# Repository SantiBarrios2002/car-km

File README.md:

# car-km — household car kilometre tracker

Logs every ride of the family car automatically and works out who drove how many kilometres each month.

A small device in the car reads distance from the OBD-II port over Bluetooth and records each ride. Tapping an NFC fob says who is driving. Rides are uploaded over WiFi to a Raspberry Pi at home, and the family uses a phone web app to see monthly totals, assign untapped rides ("that was me") and export CSV.

```
 car                                              home
┌──────────────────────────────────────┐        ┌───────────────────────────────┐
│ Vgate iCar Pro ─BLE─► ESP32-S3 module │  WiFi  │ Raspberry Pi                  │
│ (OBD-II speed)        + carrier PCB   │ ─────► │ FastAPI + SQLite (app/)       │
│ PN532 NFC ─I²C─►      (supercap hold- │  HTTP  │ web app at /, device API      │
│ (who drives)           up, 5 V input) │        │ at /api/  ◄── family phones   │
└──────────────────────────────────────┘        └───────────────────────────────┘
```

## Status

| Part | Where | State |
| --- | --- | --- |
| Pi service + web app | `app/` | **In use** on the family Pi. |
| Carrier PCB | `hardware/carrier/` | Schematic done (ERC clean); first-pass board placed, autorouted and passing DRC. **Not reviewed, not ordered.** |
| Car device firmware | `firmware/` | Not started. Conventions are already fixed in `CLAUDE.md`. |

### Next step: pre-order checks for the carrier PCB

None of these have been done yet. They come before anything is sent to a fab; details and commands are in [`hardware/README.md`](hardware/README.md#next-step-pre-order-checks).

1. **Review the board in KiCad**: placement, power trace widths, the autorouted tracks.
2. **Check the 3D fit** against Waveshare's STEP model (stack height, standoffs, cable paths).
3. **Re-run ERC and DRC** after any changes.
4. **Export the Gerber and drill files** and inspect them in a Gerber viewer.

## Repository layout

```
app/                  Pi service: FastAPI + SQLite, web app and device API
  main.py             all routes (web app + device API), sections marked with # ----
  db.py               schema and SQLite helpers
  static/index.html   the whole web app: one file, vanilla JS, Spanish/English
install.sh            Pi install: venv, systemd unit, nightly backup cron (safe to re-run)
car-km.service        systemd unit template used by install.sh
hardware/             car device hardware: Waveshare module + custom carrier PCB
  README.md           hardware design document: start here for the electronics
  carrier/            KiCad 10 project (schematic + PCB)
  bom-rev2.csv        bill of materials
  vendor/             Waveshare schematic and mechanical drawing (PDF)
CLAUDE.md             working notes for Claude Code and contributors: conventions, hard rules, hardware facts
```

`data/` (database, device token, firmware images, backups) is created at runtime and is not committed.

## Pi service

### Install on the Pi

```bash
git clone <this repo> ~/car-km
cd ~/car-km && chmod +x install.sh && ./install.sh
```

The script creates a venv, installs a systemd unit (`car-km.service`, port 8080) and a nightly SQLite backup cron, then prints the Tailscale URL to share with the family. Logs: `journalctl -u car-km -f`.

### Using it

- Open `http://<pi-tailscale-name>:8080` on a phone (see *Links*). On iOS, Share → *Add to Home Screen* makes it feel like an app.
- The first visit asks *¿Quién eres?*; the answer is remembered on that phone.
- **Ajustes**: add the people. Optionally log the real odometer reading once; after that a ride can be logged by typing the new odometer reading instead of km.
- **Apuntar**: km (or odometer) → Guardar. Rides can be back-dated.
- **Resumen**: monthly totals per person, with unassigned rides highlighted and a *Fui yo* button; the CSV button exports the month.
- Language (es/en) and €/km are set in Ajustes.

### Links (family setup)

| Where | URL |
| --- | --- |
| Anywhere, phone with Tailscale | http://iot-hub.tail8fe499.ts.net:8080 |
| Same, by Tailscale IP (if the name doesn't resolve) | http://100.102.81.29:8080 |
| Home WiFi, no Tailscale needed | http://192.168.1.140:8080 |
| API docs | http://iot-hub.tail8fe499.ts.net:8080/api/docs |

### Giving family members access (Tailscale)

At home the LAN link works for anyone on the WiFi. From outside, each person needs Tailscale. Prefer **sharing the Pi** over inviting people into the tailnet: someone you share with can reach only `iot-hub`, not your other devices.

1. In https://login.tailscale.com/admin/machines, open the **⋯** menu on `iot-hub` → **Share…** and copy the invite link.
2. Send it to the person. They install Tailscale (iOS/Android), sign in with their own Google/Apple/Microsoft account and open the link. They get their own free tailnet with `iot-hub` in it.
3. On their phone: Tailscale on → open the link above → Share / ⋮ → *Add to Home Screen*.
4. To revoke: admin console → **Machines** → `iot-hub` → **Share…** (or the **Sharing** tab) and remove them.

Alternatively, **Users → Invite users** makes them full tailnet members. That's simpler when they have many devices, but by default they can then reach every machine, so restrict them in **Access controls**.

### Device API (used by the car device)

| Method | Path | Auth | Purpose |
| --- | --- | --- | --- |
| POST | `/api/rides/batch` | bearer | JSON array of rides; idempotent on `(device_id, start_ts)` |
| GET | `/api/fobs` | none (also used by the web app) | fob → user map; send `If-None-Match` with the last ETag to get a 304 |
| GET | `/api/time` | bearer | server unix time, for setting the RTC |
| GET | `/api/firmware` | bearer | latest `firmware.bin`; send `X-Version` to get a 304 when current |

Bearer = `Authorization: Bearer <token>`. The token is in `data/device_token`, created on first start and shown in Ajustes. OTA images go in `data/firmware/` (`firmware.bin` + `version.txt`).

Ride object:

```json
{"device_id":"meriva-1","start_ts":1759742400,"end_ts":1759744230,"km":23.4,
 "fob_uid":"04A1B2C3D4E580","source":"obd","fw":"0.3.1","end_reason":"brownout"}
```

Interactive docs at `/api/docs`.

### Development

```bash
python3 -m venv .venv && .venv/bin/pip install -r requirements.txt
.venv/bin/uvicorn app.main:app --reload --port 8081
```

Port 8081 lets the dev server run alongside the live service on 8080. Run from the repo root: the default paths under `data/` are relative to the working directory.

### Security model

There are no logins: the app is reachable only on the home LAN and over Tailscale, and a household km log doesn't need more. The device API uses a bearer token. Don't expose port 8080 to the internet; if wider access is ever needed, put it behind Tailscale Serve or a reverse proxy with authentication.

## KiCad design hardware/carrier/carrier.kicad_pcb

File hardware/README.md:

# car-km hardware — Rev 2: Waveshare ESP32-S3-Touch-LCD-2.8 + carrier PCB

The car device is an off-the-shelf **Waveshare ESP32-S3-Touch-LCD-2.8** (ESP32-S3, 2.8" touch display, RTC, Li-ion charger) mounted on a small custom **carrier PCB**. The carrier takes 5 V from the car's USB port, holds the module up for a few seconds after the ignition cuts power (so the ride can be saved), tells the firmware when that happens, and breaks out the PN532 NFC reader and a debug UART. Distance comes from a **Vgate iCar Pro** BLE OBD-II dongle, which needs no wiring.

## Status

| Item | State |
| --- | --- |
| Module facts | Verified against Waveshare's schematic and 2D drawing (`vendor/`), 2026-10-06. |
| Carrier schematic | `carrier/carrier.kicad_sch`, KiCad 10, ERC clean (0 violations). |
| Carrier PCB | `carrier/carrier.kicad_pcb`, first pass: placed, autorouted, DRC clean. **Not reviewed by a person, not ordered.** |
| Parts | Nothing bought yet except the OBD dongle (`bom-rev2.csv`). |

## Next step: pre-order checks

None of these have been done yet. Work through them in order before sending anything to a fab. All commands run from the repo root.

**1. Review the board in KiCad.** Open `hardware/carrier/carrier.kicad_pro`, then the PCB editor. Look at:
- **Routing:** the signals were autorouted (Freerouting) and nobody has looked at them yet. Tidy anything odd, especially the long USB_5V run to the fallback R3/D2. Those two parts aren't fitted by default, so that track could be shortened or moved.
- **Power trace widths:** 0.6 mm, which is the most J3's 1.0 mm-pitch pads and J1's VBUS pins allow. Widen the open runs (J1 → F1 → D1/JP1 → J3, J5 → JP2 → caps) where there is room.
- **Connector positions** against the real stack (see step 2): J1 on the bottom edge, J3 on the left edge, J5 on the right edge, J2 on the top edge.
- **Silkscreen:** pin-1 marks, cap polarity, the JP1/JP2 notes.
- After any edit, refill zones (`B`) before checking.

**2. Check the 3D fit.**
- Install the 3D models (`sudo apt install kicad-packages3d`, or use a KiCad install that has them).
- Download `ESP32-S3-Touch-LCD-2.8_3D.zip` from the [Waveshare wiki](https://www.waveshare.com/wiki/ESP32-S3-Touch-LCD-2.8) into `vendor/`. Don't commit it; it's 20 MB.
- Export the carrier: `kicad-cli pcb export step --subst-models -o hardware/carrier/carrier.step hardware/carrier/carrier.kicad_pcb`.
- Combine the two in FreeCAD (or the KiCad 3D viewer): the module sits on top, parts side facing the carrier, on 8 mm standoffs. Check:
  - **The gap between the boards.** The module's back parts are 6 mm tall, so about 2 mm is left. The carrier's inner face has no parts, but the through-hole leads of J2, J4, C1 and C4 stick out of it: trim them flush or check they clear.
  - **Total depth:** module 10 mm + standoffs 8 mm + carrier 1.6 mm + supercaps 20 mm standing (or ~9 mm lying flat).
  - **Cable paths:**
    - SH-12 cable from J3 round the left edge to module J8, which is in the lower-left quadrant of the module's back, about 12 mm from its left edge;
    - 2-pin cable from J5 to module J1 (BAT);
    - PN532 cable from J2.
  - **USB-C clearance:** a plug in the carrier's J1 near the module's own USB-C, which sits bottom centre.

**3. Re-run ERC and DRC** after any change:

```bash
kicad-cli sch erc --severity-all -o /tmp/erc.rpt hardware/carrier/carrier.kicad_sch
kicad-cli pcb drc --schematic-parity --severity-all -o /tmp/drc.rpt hardware/carrier/carrier.kicad_pcb
```

Expected: ERC 0 violations; DRC 0 errors, 0 unconnected, 0 parity issues. Two warnings are accepted: J1's library silkscreen runs off the board edge where the receptacle overhangs it.

**4. Export the fab files and inspect them.**

```bash
mkdir -p hardware/carrier/fab
kicad-cli pcb export gerbers --check-zones -l F.Cu,B.Cu,F.Paste,B.Paste,F.SilkS,B.SilkS,F.Mask,B.Mask,Edge.Cuts \
  -o hardware/carrier/fab/ hardware/carrier/carrier.kicad_pcb
kicad-cli pcb export drill --excellon-separate-th --generate-map -o hardware/carrier/fab/ hardware/carrier/carrier.kicad_pcb
```

Open the result in `gerbview` (ships with KiCad) or the fab's online viewer before uploading. The board is 2 layers, 1.6 mm, 69.0 × 49.9 mm, with a 0.2 mm minimum clearance and 0.15 mm minimum track (standard JLCPCB/PCBWay rules). `fab/` is not committed.

**After the boards arrive** (before the first car test):
- Change the module's R7 to ≥ 200 kΩ (see *Charge current*).
- Do the bench checks under *Still to verify*.

## The Waveshare module (from its schematic)

| Item | Fact | Consequence |
| --- | --- | --- |
| J8 "12-pin header" | **JST SH 1.0 mm, 12 pins** (`SH1.0-12P`) | The carrier connects with a 12-way SH cable; its J3 is an SH-12 socket. |
| J8 pinout | 1 GND · 2 **USB_5V** · 3 D− (IO19) · 4 D+ (IO20) · 5 GND · 6 3V3 · 7 SCL (IO10) · 8 SDA (IO11) · 9 UART_TXD (IO43) · 10 UART_RXD (IO44) · 11 **GPIO18** · 12 **GPIO15** | 5 V in, I²C, two spare GPIOs and UART on one cable. |
| USB → system | USB_5V → **D3 B5819WS** Schottky → VCC → **ME6217C33** LDO → 3V3 | USB has priority; VCC ≈ USB_5V − 0.3 V. D3 stops the battery rail back-feeding USB_5V. |
| Battery → system | BAT → **Q1 AO3401** (gate: R2 100 k to BAT, pulled low by **T2** when `BAT_Control` = IO7 is high, or by Key1) → **Q2 AO3401** (gate = USB_5V, R29 100 k to GND) → VCC | The battery path is on only when USB is absent **and** the firmware has driven IO7 high. Q2's body diode also conducts once VCC drops ~0.6 V below BAT. |
| Charger | **ETA6098** switching Li-ion charger, input = USB_5V, **RISET R7 = 82 kΩ → 2 A**, CV 4.2 V, 130 mA termination, restarts at −160 mV, input 4.5–5.5 V | Charges whatever is on the battery connector to 4.2 V. |
| Battery connector | J1, labelled **"PH1.25 2P"**: the 1.25 mm MX1.25 / Molex PicoBlade-compatible part (not JST PH 2.0 or GH). Pin 1 = BAT. | The supercap bank plugs in here, via the carrier's J5. |
| Pull-ups | R30 10 k to 3V3 on IO15 (SD_D2), R35 10 k on IO18 (SD_D1) | IO15 already has a pull-up, so the power-loss sense must drive it actively low. |
| BAT_ADC | IO8 reads BAT through 200 k / 100 k | Vbat = 3 × Vadc. |
| Backlight | NPN T3 on **IO5** | Turned off first when power is lost. |
| Antenna | Ceramic chip antenna (CA-C03) + U.FL, **top-left corner** in back view (ESP32 module upper-left, USB-C bottom centre) | Copper keep-out on the carrier under that corner. |
| Mechanical | PCB 69.00 × 49.90 mm, glass 73.06 × 50.54 mm, 10.0 mm total, **6.0 mm of parts on the back**. 4 holes on a **60.00 × 41.00 mm** grid, 4.50 mm in from the edges, Ø ≈ 2.7 mm (M2.5) | The carrier copies the outline and holes; standoffs ≥ 8 mm. |

## Carrier design

Schematic: `carrier/carrier.kicad_sch` (the source of truth for every net).

```
car USB ─ J1 USB-C ─ F1 PTC 1.1 A ─┬─ TVS1 SMAJ5.0A ─ GND
            VIN_CAR      VIN_FUSED ├─ R8 4k7 bleeder ─ GND
                                   ├─ R1 100k ─┬─ R2 11k3 ─ GND
                                   │           └─ U2 TPS3808G01 SENSE      ~RESET → J3.12 (IO15) = PWR_SENSE
                                   │              (VDD = module 3V3 via J3.6, C3 100n)
                                   └─ D1 SS34 ∥ JP1 (bridged) ─┬─ C2 10µF   USB_5V → J3.2
                                                               └─ TP1

module J1 (BAT) ─ cable ─ J5 PicoBlade ─ JP2 (bridged) ─ C1 5F/2.7V ─┬─ C4 5F/2.7V ─ GND
                                                          R4 10k ∥ C1  R5 10k ∥ C4
```

The carrier only protects (F1, TVS1), senses (U2), balances (R4/R5) and connects. Charging and switching to the caps happen on the module.

- **Hold-up.** The module's ETA6098 charges the 2 × 5 F bank (2.5 F, 5.4 V rated) to 4.2 V. When the car cuts power, USB_5V collapses (R8 bleeds it down; the module's D3 stops the board holding it up), Q2 turns on and the board runs from the caps. **Hold-up ≈ 5–7 s** with the backlight off: 2.5 F × (4.2 − 3.6 V) ÷ 0.2 A ≈ 7 s from a full bank, less because the charger only tops up after a 160 mV drop (~4.04 V). Saving the ride takes well under a second.
- **Power-loss sense (U2).** A TPS3808G01 supervisor watches VIN_FUSED through R1/R2 and drives IO15 low with its open-drain `~RESET`; the module's R30 is the pull-up.
  - Trip point: 0.405 V × (1 + 100 k / 11.3 k) = **3.99 V falling**. `~RESET` releases 20 ms after VIN_FUSED recovers (CT open).
  - U2 runs from the module's 3V3, which the caps hold up, so IO15 stays low for the whole hold-up. A supervisor powered from the car side would let IO15 float back high once the car rail fell below ~1 V.
  - A plain resistor divider can't do this job: R30 keeps IO15 high whether the car is on or off.
- **JP1 is bridged by default** (D1 bypassed). D1's drop plus the PTC and cable would leave ~4.4 V at J8, below the ETA6098's 4.5 V minimum input. D1 only matters in the fallback configuration.
- **Charge current.** Everything the module draws, up to 2 A of charge current included, comes in through J8 pin 2: one SH contact rated about 1 A, behind F1 (1.1 A hold). **Change the module's R7 (0402, back side) from 82 k to ≥ 200 k (≈ 0.8 A)** before the first car test. Recharging an empty bank then takes ~15 s instead of ~5 s.
- **Firmware duties:** drive IO7 (`BAT_Control`) high at boot and never low, otherwise the caps are never connected. Leave the microSD slot empty or use 1-bit SD mode, because IO15 is also SD_D2.

### Fallback configuration

This is for the case where the bench test shows the module's charger misbehaving with a capacitor load. Footprints for the Rev 1 circuit are on the board, unpopulated (DNP):
- **R3** (22 Ω, 1 W) from USB_5V to VCAP;
- **D2** (SS34) from VCAP back to USB_5V.

To switch over:
1. Cut JP1, so that D1 blocks back-feed into the car port.
2. Cut JP2.
3. Leave J5 unconnected.
4. Fit R3 and D2.

The caps then charge to ~4.7 V from the 5 V side and discharge into USB_5V through D2. Hold-up ≈ 2.5 F × (4.4 − 3.9 V) ÷ 0.2 A ≈ 6 s.

### Nets (summary)

| Net | Pins |
| --- | --- |
| VIN_CAR | J1 VBUS (A4, A9, B4, B9), F1.1 |
| VIN_FUSED | F1.2, TVS1 K, D1 A, JP1.1, R1.1, R8.1 |
| USB_5V | D1 K, JP1.2, C2.1, J3.2, TP1, R3.1 (DNP), D2 K (DNP) |
| SENSE_DIV | R1.2, R2.1, U2.5 SENSE |
| PWR_SENSE | U2.1 ~RESET, J3.12 |
| BAT | J5.1, JP2.1 |
| VCAP | JP2.2, C1 +, R4.1, TP2, R3.2 (DNP), D2 A (DNP) |
| VCAP_MID | C1 −, C4 +, R4.2, R5.1 |
| +3V3 | J3.6, J2.1, U2.6 VDD, U2.3 ~MR, C3.1 |
| SCL / SDA | J3.7 / J3.8 → J2.4 / J2.3 |
| NFC_IRQ | J3.11, J2.5 |
| UART_TX / UART_RX | J3.9 / J3.10 → J4.1 / J4.2 (module TXD / RXD) |
| USB_CC1 / USB_CC2 | J1 A5 / B5 → R6 / R7 5.1 k → GND |
| GND | J1 GND + shell, TVS1 A, R2, R5, R6, R7, R8, C2, C3, C4 −, U2.2, J2.2, J3.1, J3.5, J3/J5 mounting tabs, J4.3, J5.2, H2–H4 |

Not connected: J3.3 / J3.4 (USB D±), U2.4 CT (open = 20 ms delay), J1 D± and SBU. H1 is a bare hole.

### Connectors and cables

| Ref | Part | Mates with | Cable |
| --- | --- | --- | --- |
| J1 | USB-C 16-pin receptacle (HRO TYPE-C-31-M-12), power only | car USB cable | — |
| J3 | JST **SM12B-SRSS-TB** (SH 1.0 mm, 12-pin, side entry) | module J8 | 12-way SH, 80–120 mm, **same-side (type A)** so pin 1 maps to pin 1. Check with a meter before first power-up. |
| J5 | Molex **53261-0271** (PicoBlade 1.25 mm, 2-pin, SMD right angle) | module J1 (BAT) | 2-way 1.25 mm (Molex 51021-0200 housing both ends), 80 mm. Mind polarity: pin 1 = BAT on both. |
| J2 | JST **S5B-PH-K-S** (PH 2.0 mm, 5-pin, right angle) | PN532 module (DIP switch set to I²C) | 5-way PH to Dupont, 150–250 mm. Pins: 3V3, GND, SDA, SCL, IRQ. |
| J4 | 1 × 3 2.54 mm header | USB-UART dongle | J4.1 = module TX → dongle RX, J4.2 = module RX ← dongle TX, J4.3 = GND. |

## PCB layout (`carrier/carrier.kicad_pcb`)

- **Outline and stack:**
  - 69.00 × 49.90 mm, R2 corners, 2 layers, 1.6 mm.
  - The module sits on top, parts side down, on **8 mm M2.5 standoffs**; the carrier is behind it.
  - KiCad's top view is the carrier's outer face, which matches the module's back view: antenna top-left, USB-C bottom.
- **All parts are on the outer face** (F.Cu). The inner face stays empty because only ~2 mm is left under the module's 6 mm-tall back parts.
- **Holes:** Ø2.7 at (4.5, 4.5), (64.5, 4.5), (4.5, 45.5), (64.5, 45.5) in module coordinates (origin at the bottom-left, back view).
  - H1, top-left, sits inside the antenna keep-out and is a bare NPTH with no copper.
  - H2–H4 are plated and tied to GND.
- **Antenna keep-out:** 25 × 12 mm in the top-left corner, no copper on either layer, outlined on the silkscreen.
- **Placement:**
  - edges: J1 on the bottom edge, J3 on the left edge (opening outward, cable wraps round to J8), J5 on the right edge, J2 on the top edge right of the keep-out;
  - J4 bottom right;
  - supercaps C1/C4 top right;
  - car-input parts (F1, TVS1, D1/JP1) between J1 and J3;
  - sense circuit (U2, R1/R2, C3) next to J3.
- **Net classes** (stored in `carrier.kicad_pro`):

  | Class | Track | Via | Nets |
  | --- | --- | --- | --- |
  | Power | 0.6 mm | 0.8 / 0.4 mm | VIN_CAR, VIN_FUSED, USB_5V, BAT, VCAP, VCAP_MID |
  | GND | 0.4 mm | 0.6 / 0.3 mm | GND |
  | Default | 0.25 mm | 0.6 / 0.3 mm | all signals |

  Clearance is 0.2 mm everywhere. The 0.15 mm minimum track width allows the necked-down +3V3 entry into U2's SOT-23 pads.
- **GND:**
  - pours on both layers;
  - a fan-out via next to every SMD GND pad;
  - stitching vias across the board.
  F.Cu has track keep-outs under the J1, J3 and J5 bodies.
- **Routing:** Freerouting 2.5 via Specctra DSN/SES, with GND left to the pours. This is a first pass to tidy by hand (step 1 of the pre-order checks).

## Firmware hooks (ESP-IDF, Waveshare BSP)

| Signal | GPIO | Use |
| --- | --- | --- |
| BAT_Control | IO7 | **Output high at boot**, first line of `app_main`. Keeps Q1 on so the caps carry the board when power is lost. |
| BAT_ADC | IO8 | Vbat = 3 × Vadc. Show "backup OK" above 3.9 V; warn if the caps never reach 4.0 V. |
| PWR_SENSE | IO15 | Input; falling edge = car power lost → brownout handler. |
| LCD_BL | IO5 | Backlight; switched off first in the brownout handler. |
| NFC_IRQ | IO18 | Input; falling edge = PN532 has a tag. |
| I²C | IO10 SCL / IO11 SDA | Shared: PN532 0x24, PCF85063 RTC 0x51, QMI8658 IMU 0x6B. |
| Key_BAT | IO6 | Module button; unused. |

Brownout handler: backlight off → stop BLE polling → write `ride/live` → mark the ride closed → halt (`while (1) vTaskDelay`). In the halt loop, if IO15 reads high again (ignition back on while the caps still hold the board, so no power-on reset happens), call `esp_restart()`; U2's 20 ms release delay debounces this. On the next boot a leftover `ride/live` is closed and queued.

## Still to verify

Verified from Waveshare's files: J8 pitch and pinout, USB_5V on J8, power path, charger current, outline and hole grid, antenna position, IO15/IO18 pull-ups.

- [ ] Hole diameter: the STEP only shows a 4.3 mm ring. Measure it, or use Ø2.7 / M2.5 either way.
- [ ] Bench, supercaps:
  1. Caps on module J1, USB in; BAT should reach ~4.2 V (BAT_ADC or a meter).
  2. Set IO7 high, pull USB and time the hold-up with the backlight off. Target ≥ 5 s.
  3. Repeat on a 1 A-limited supply to imitate a weak car port.
- [ ] Bench: module current with backlight on/off and WiFi on/off (USB meter).
- [ ] SH cable is same-side (type A): check with a meter before first power-up.
- [ ] The car's USB port really goes dead at key-out.

## Bill of materials

`bom-rev2.csv`. Revision notes:
- **First Rev 2 draft:**
  - J3 is an SH-12 socket (not 2.54 mm);
  - J5 1.25 mm added;
  - D1 kept but bypassable;
  - R3/D2 kept as fallback footprints;
  - SH and 1.25 mm cables added.
- **2026-10-06 review (schematic rev A):**
  - U2 TPS3808G01 + C3 power-loss sense (R2 47 k → 11.3 k);
  - R8 4.7 k bleeder;
  - JP1 bridged by default;
  - J5 = Molex 53261-0271;
  - supercaps renamed C1a/C1b → C1/C4;
  - H1 changed to a bare NPTH;
  - holes, jumpers and test points dropped from the BOM.

## Later: Rev 2b

PN532 chip with a printed antenna on the carrier (NXP AN1445). This needs a NanoVNA for antenna tuning, and only makes sense once Rev 2 works.

## Sources

- Waveshare [ESP32-S3-Touch-LCD-2.8 wiki](https://www.waveshare.com/wiki/ESP32-S3-Touch-LCD-2.8): schematic and 2D drawing, copied into `vendor/` as `ESP32-S3-Touch-LCD-2.8_schematic.pdf` and `ESP32-S3-Touch-LCD-2.8_2D.pdf`; STEP model (not committed).
- ETA6096 datasheet via [LCSC](https://wmsc.lcsc.com/wmsc/upload/file/pdf/v2/lcsc/2307171444_etasolution-ETA6096D3K_C7465538.pdf). It is the same family as the module's ETA6098: RISET 82 k → 2 A, CV 4.2 V, 130 mA termination, 4.5–5.5 V input.
- TI TPS3808 datasheet: adjustable version (G01) with a 0.405 V threshold, open-drain `~RESET`, CT open = 20 ms delay.

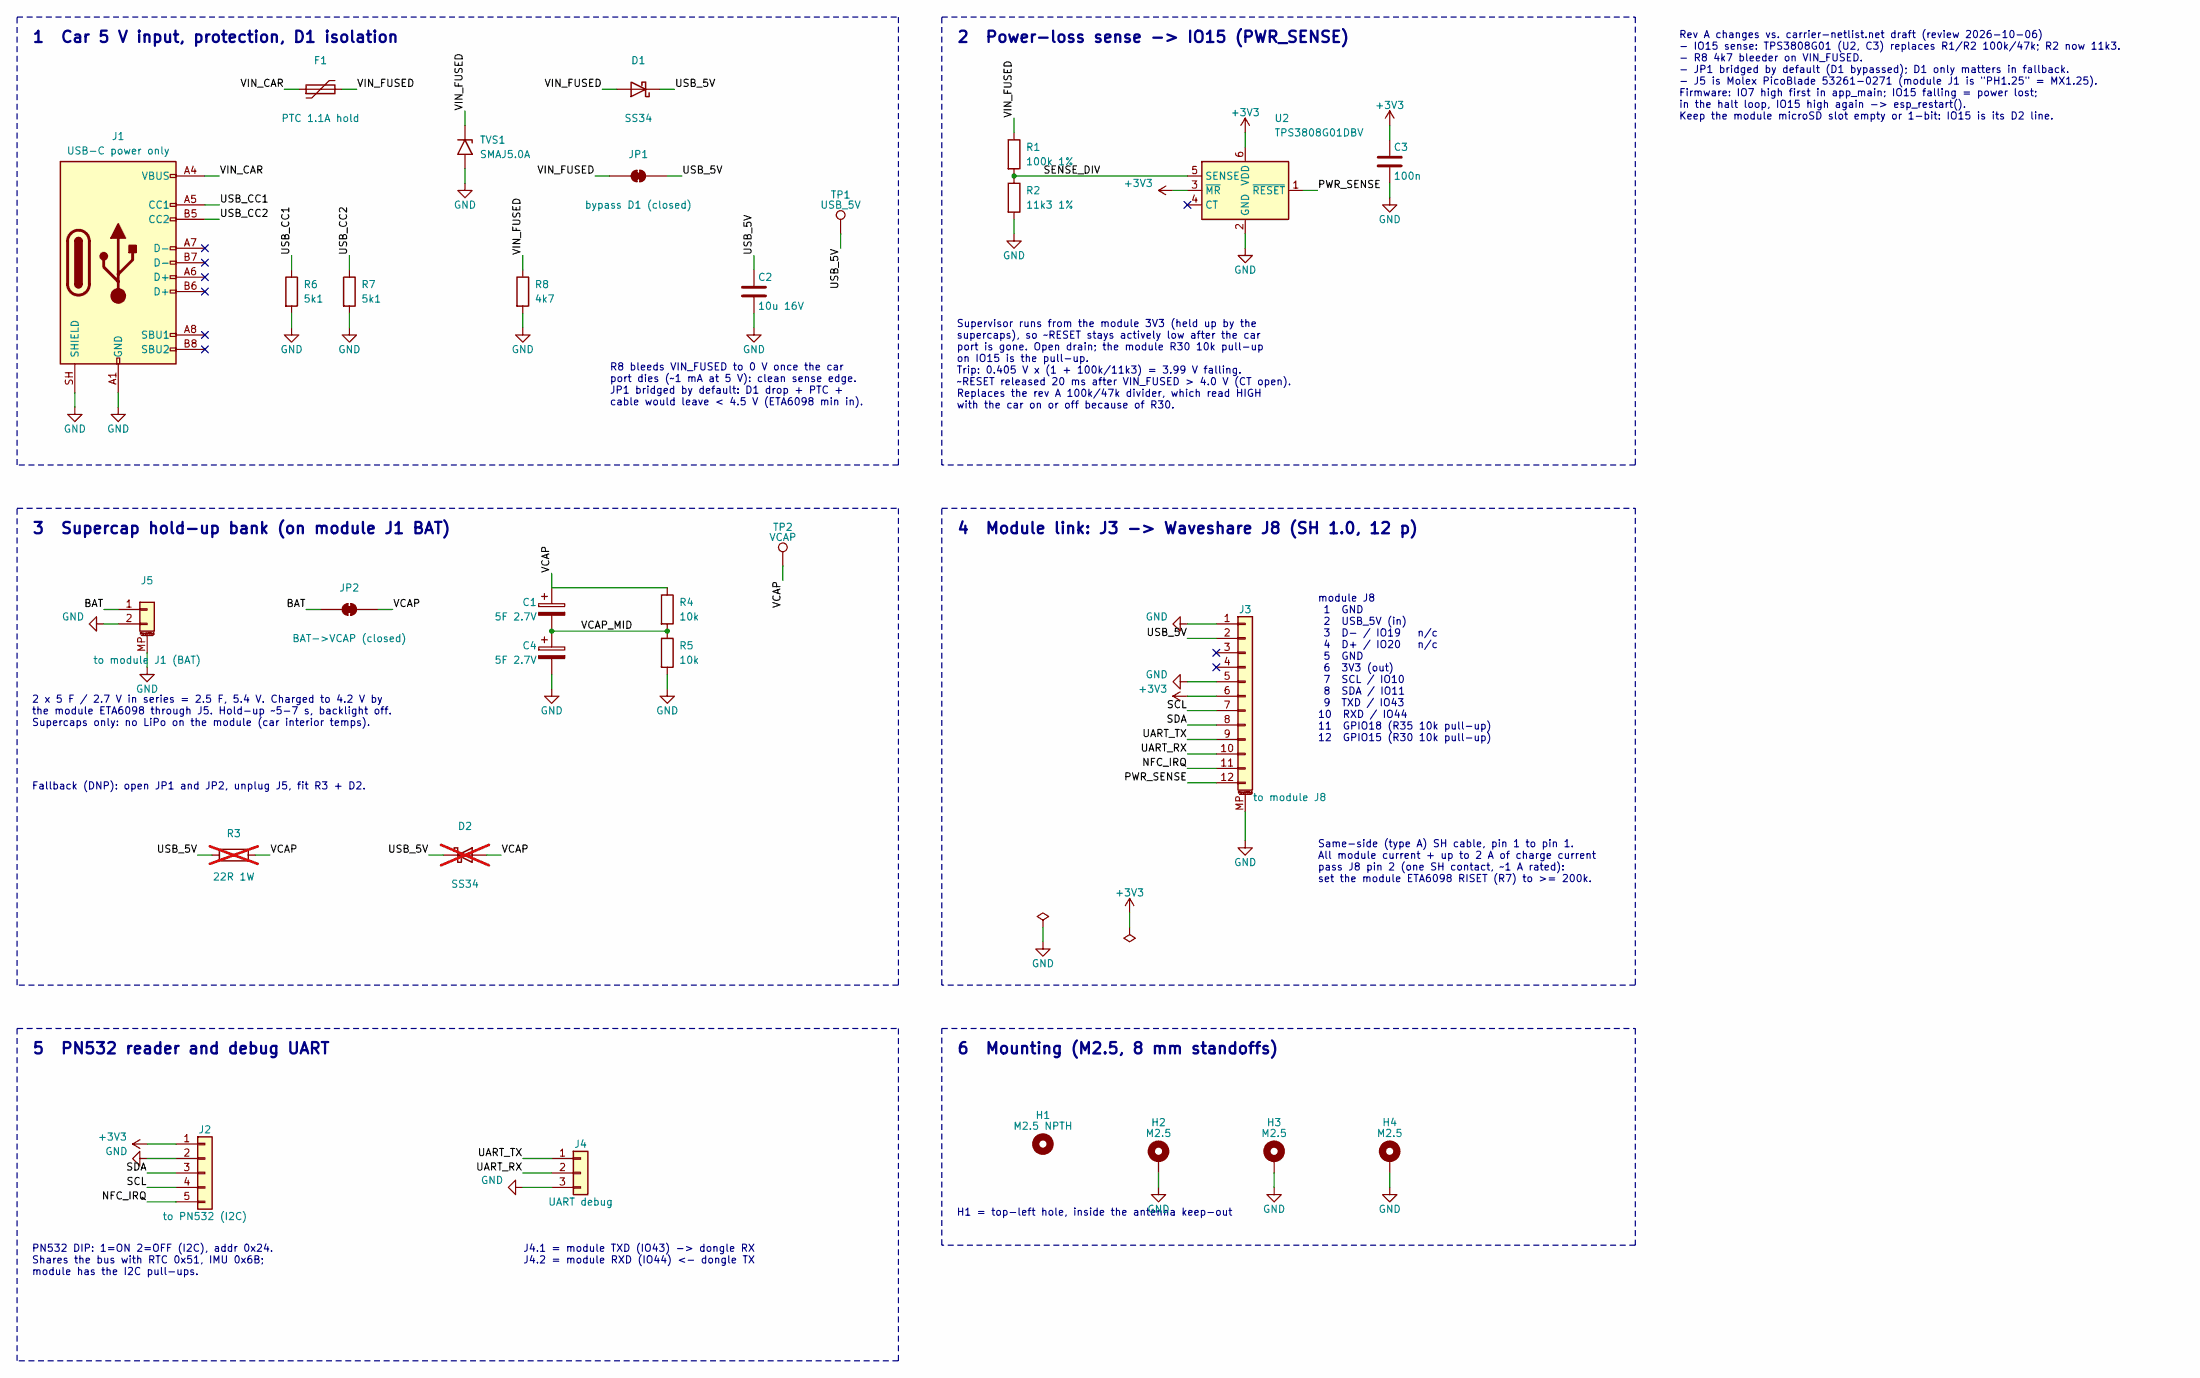
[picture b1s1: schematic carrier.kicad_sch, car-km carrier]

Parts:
C1, C4: 5F 2.7V; CP_Radial_D8.0mm_P3.50mm; MPN Eaton HB0820-2R5505-R class, ESR <= 0.5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
C2: 10u 16V; C_0805_2012Metric
C3: 100n; C_0805_2012Metric
D1: SS34; D_SMA
D2: SS34; D_SMA; not fitted
F1: PTC 1.1A hold; Fuse_1812_4532Metric
H1: M2.5 NPTH; MountingHole_2.7mm_M2.5
H2, H3, H4: M2.5; MountingHole_2.7mm_M2.5_Pad
J1: USB-C power only; USB_C_Receptacle_HRO_TYPE-C-31-M-12; MPN HRO TYPE-C-31-M-12
J2: to PN532 (I2C); JST_PH_S5B-PH-K_1x05_P2.00mm_Horizontal; MPN JST S5B-PH-K-S
J3: to module J8; JST_SH_SM12B-SRSS-TB_1x12-1MP_P1.00mm_Horizontal; MPN JST SM12B-SRSS-TB
J4: UART debug; PinHeader_1x03_P2.54mm_Vertical
J5: to module J1 (BAT); Molex_PicoBlade_53261-0271_1x02-1MP_P1.25mm_Horizontal; MPN Molex 53261-0271
JP1: bypass D1 (closed); SolderJumper-2_P1.3mm_Bridged_RoundedPad1.0x1.5mm
JP2: BAT->VCAP (closed); SolderJumper-2_P1.3mm_Bridged_RoundedPad1.0x1.5mm
R1: 100k 1%; R_0805_2012Metric
R2: 11k3 1%; R_0805_2012Metric
R3: 22R 1W; R_2512_6332Metric; not fitted
R4, R5: 10k; R_0805_2012Metric
R6, R7: 5k1; R_0805_2012Metric
R8: 4k7; R_0805_2012Metric
TP1: USB_5V; TestPoint_Pad_D1.5mm
TP2: VCAP; TestPoint_Pad_D1.5mm
TVS1: SMAJ5.0A; D_SMA
U2: TPS3808G01DBV; SOT-23-6; MPN TPS3808G01DBVR

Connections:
+3V3: C3.1, J2.1, J3.6, U2.3 (~MR), U2.6 (VDD)
/BAT: J5.1, JP2.1 (A)
/NFC_IRQ: J2.5, J3.11
/PWR_SENSE: J3.12, U2.1 (~RESET)
/SCL: J2.4, J3.7
/SDA: J2.3, J3.8
/SENSE_DIV: R1.2, R2.1, U2.5 (SENSE)
/UART_RX: J3.10, J4.2
/UART_TX: J3.9, J4.1
/USB_5V: C2.1, D1.1 (K), D2.1 (K), J3.2, JP1.2 (B), R3.1, TP1.1
/USB_CC1: J1.A5 (CC1), R6.1
/USB_CC2: J1.B5 (CC2), R7.1
/VCAP: C1.1, D2.2 (A), JP2.2 (B), R3.2, R4.1, TP2.1
/VCAP_MID: C1.2, C4.1, R4.2, R5.1
/VIN_CAR: F1.1, J1.A4 (VBUS), J1.A9 (VBUS), J1.B4 (VBUS), J1.B9 (VBUS)
/VIN_FUSED: D1.2 (A), F1.2, JP1.1 (A), R1.1, R8.1, TVS1.1 (A1)
GND: C2.2, C3.2, C4.2, H2.1, H3.1, H4.1, J1.A1 (GND), J1.A12 (GND), J1.B1 (GND), J1.B12 (GND), J1.SH (SHIELD), J2.2, J3.1, J3.5, J3.MP (MountPin), J4.3, J5.2, J5.MP (MountPin), R2.2, R5.2, R6.2, R7.2, R8.2, TVS1.2 (A2), U2.2 (GND)

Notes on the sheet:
Rev A changes vs. carrier-netlist.net draft (review 2026-10-06) - IO15 sense: TPS3808G01 (U2, C3) replaces R1/R2 100k/47k; R2 now 11k3. - R8 4k7 bleeder on VIN_FUSED. - JP1 bridged by default (D1 bypassed); D1 only matters in fallback. - J5 is Molex PicoBlade 53261-0271 (module J1 is "PH1.25" = MX1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
1 Car 5 V input, protection, D1 isolation
6 Mounting (M2.5, 8 mm standoffs)
2 Power-loss sense -> IO15 (PWR_SENSE)
R8 bleeds VIN_FUSED to 0 V once the car port dies (~1 mA at 5 V): clean sense edge. JP1 bridged by default: D1 drop + PTC + cable would leave < 4.5 V (ETA6098 min in).
2 x 5 F / 2.7 V in series = 2.5 F, 5.4 V. Charged to 4.2 V by the module ETA6098 through J5. Hold-up ~5-7 s, backlight off. Supercaps only: no LiPo on the module (car interior temps).
H1 = top-left hole, inside the antenna keep-out
4 Module link: J3 -> Waveshare J8 (SH 1.0, 12 p)
5 PN532 reader and debug UART
Supervisor runs from the module 3V3 (held up by the supercaps), so ~RESET stays actively low after the car port is gone. Open drain; the module R30 10k pull-up on IO15 is the pull-up. Trip: 0.405 V x (1 + 100k/11k3) = 3.99 V falling. ~RESET released 20 ms after VIN_FUSED > 4.0 V (CT open). Replaces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
PN532 DIP: 1=ON 2=OFF (I2C), addr 0x24. Shares the bus with RTC 0x51, IMU 0x6B; module has the I2C pull-ups.
3 Supercap hold-up bank (on module J1 BAT)
Same-side (type A) SH cable, pin 1 to pin 1. All module current + up to 2 A of charge current pass J8 pin 2 (one SH contact, ~1 A rated): set the module ETA6098 RISET (R7) to >= 200k.
J4.1 = module TXD (IO43) -> dongle RX J4.2 = module RXD (IO44) <- dongle TX
module J8 1 GND 2 USB_5V (in) 3 D- / IO19 n/c 4 D+ / IO20 n/c 5 GND 6 3V3 (out) 7 SCL / IO10 8 SDA / IO11 9 TXD / IO43 10 RXD / IO44 11 GPIO18 (R35 10k pull-up) 12 GPIO15 (R30 10k pull-up)
Fallback (DNP): open JP1 and JP2, unplug J5, fit R3 + D2.

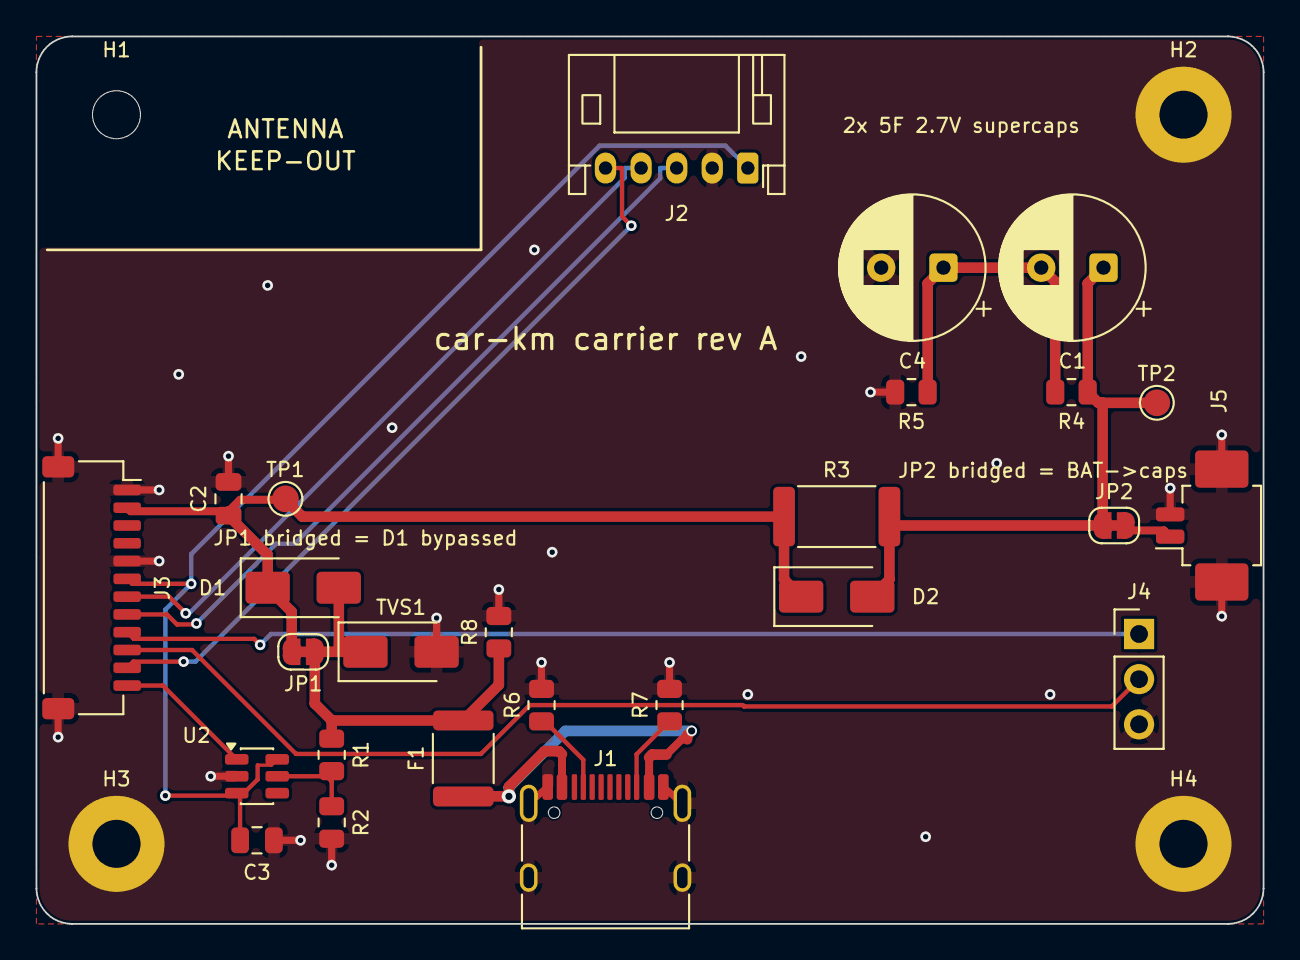
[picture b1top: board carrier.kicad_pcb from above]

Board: 2 copper layers, 69.0 x 49.9 mm, 30 parts (0 on the bottom side), 17 nets.
